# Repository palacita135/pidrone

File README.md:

# pidrone
python scripts for dronekit

Setup first your quad with good PID setting before using dronekit

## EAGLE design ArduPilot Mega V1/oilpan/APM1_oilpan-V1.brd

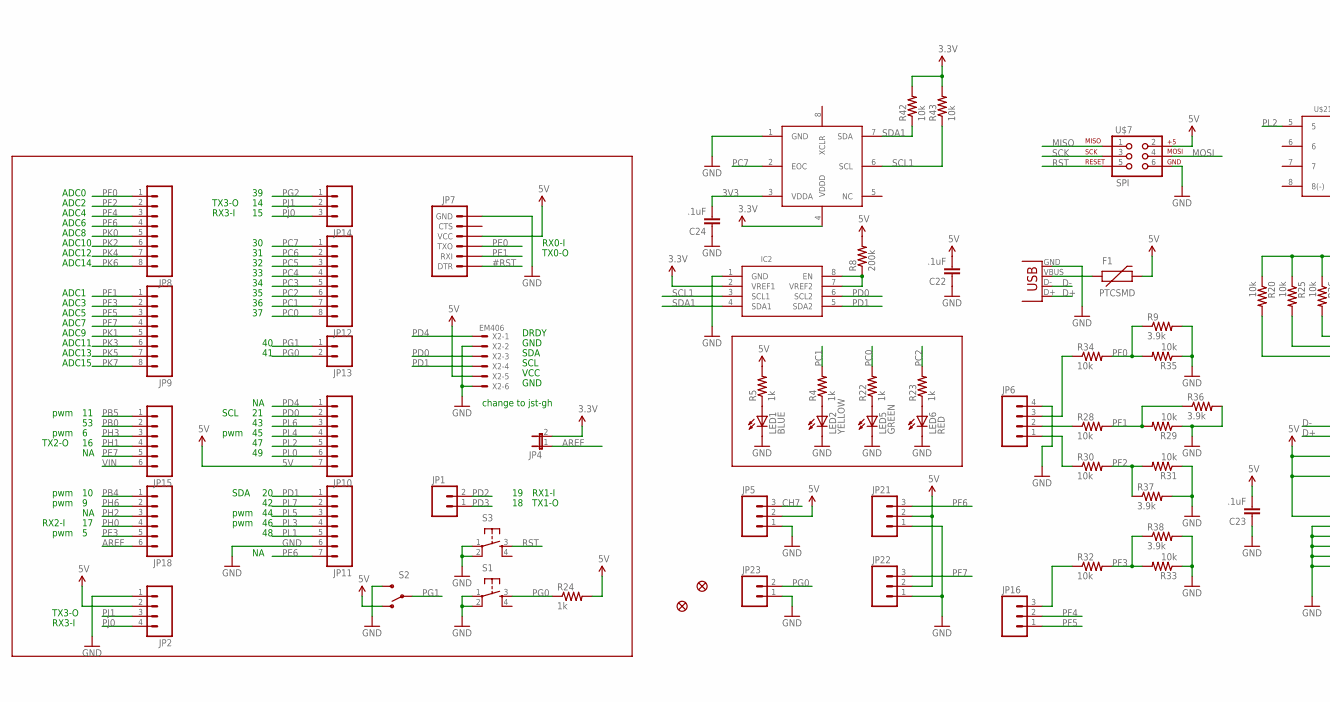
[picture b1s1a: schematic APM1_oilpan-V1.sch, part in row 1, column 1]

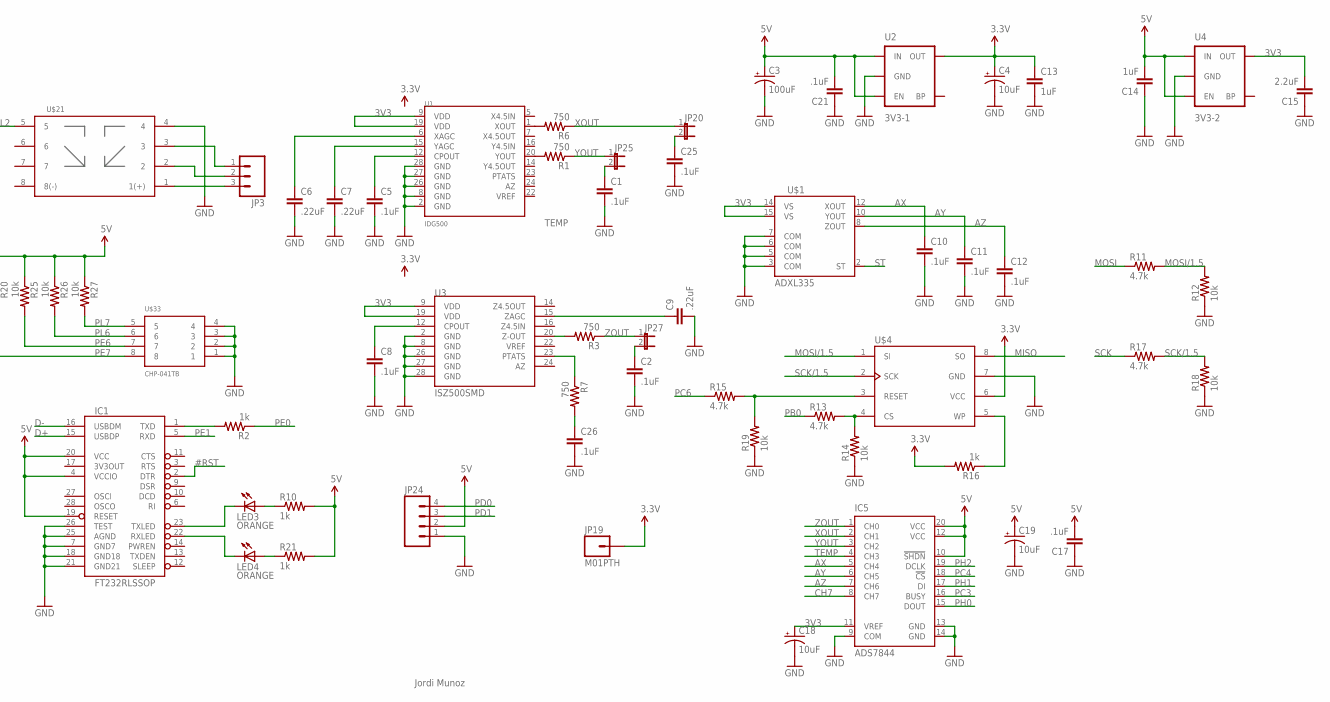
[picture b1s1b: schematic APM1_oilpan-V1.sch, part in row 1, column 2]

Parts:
C1, C2, C5, C8, C10, C11, C12, C17, C21, C22, C23, C24, C25, C26: .1uF; C0402
C3: 100uF; EIA3528
C4, C18, C19: 10uF; EIA3216
C6, C7, C9: .22uF; C0402
C13, C14: 1uF; C0402
C15: 2.2uF; C0402
F1: PTCSMD; PTC-1206
IC1: FT232RLSSOP; SSOP28DB
IC2: PCA9306; SOIC8
IC5: ADS7844; SSOP20BU
JP1, JP13, JP23: M02PTH; 1X02
JP2, JP6, JP24: M04PTH; 1X04
JP3, JP5, JP14, JP16, JP21, JP22: M03PTH; 1X03
JP4, JP20, JP25, JP27: JUMPER-2SMD-NO; SJ_2S-NO
JP7: ARDUINO_SERIAL_PROGRAMPTH; 1X06
JP8, JP9, JP12: M08; 1X08
JP10, JP11: M07; 1X07
JP15, JP18: M06SIP; 1X06
JP17, JP26: FIDUCIAL1X2.5; FIDUCIAL-1X2.5
JP19: M01PTH; 1X01
LED1: BLUE; LED-0603
LED2: YELLOW; LED-0603
LED3, LED4: ORANGE; LED-0603
LED5: GREEN; LED-0603
LED6: RED; LED-0603
R1, R3, R6, R7: 750; C0402
R2, R4, R5, R10, R16, R21, R22, R23, R24: 1k; C0402
R8: 200k; C0402
R9, R36, R37, R38: 3.9k; C0402
R11, R13, R15, R17: 4.7k; C0402
R12, R14, R18, R19, R20, R25, R26, R27, R28, R30, R32, R34, R42, R43: 10k; C0402
R29, R31, R33, R35: 10k; AXIAL-0.3
S1, S3: TAC_SWITCHSMD; TACTILE_SWITCH_SMD
S2: SWITCH-SPSTSMD2; SWITCH-SPDT-SMD
U1: IDG500; QFN-28_6X8
U2: 3V3-1; SOT23-5
U3: ISZ500SMD; QFN-28_6X8
U4: 3V3-2; SOT23-5
U$1: ADXL335; LFCSP-16
U$4: DF; SO08WIDE
U$7: SPI; 2X3-NS
U$8: BMP085
U$21: RELAY_23
U$33: CHP-041TB
X1: USBSMD; USB-MINIB
X2: EM406; GH-06V

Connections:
3.3V: C4.A (+), C13.1, IC2.2 (VREF1), JP4.2, JP19.1, R16.2, R42.2, R43.2, U2.5 (OUT), U$4.6 (VCC), U$8.4 (VDDD)
3V3: C15.2, C18.A (+), C24.2, IC5.11 (VREF), U1.9 (VDD), U1.19 (VDD), U3.9 (VDD), U3.19 (VDD), U4.5 (OUT), U$1.14 (VS), U$1.15 (VS), U$8.3 (VDDA)
5V: C3.A (+), C14.2, C17.2, C19.A (+), C21.2, C22.2, C23.2, F1.2, IC1.4 (VCCIO), IC1.19 (RESET), IC1.20 (VCC), IC5.10 (!SHDN), IC5.12 (VCC), IC5.20 (VCC), JP2.2, JP5.2, JP7.4 (VCC), JP10.7, JP21.2, JP22.2, JP24.2, R5.2, R8.2, R10.2, R20.1, R21.2, R24.2, R25.1, R26.1, R27.1, S2.1 (O), U2.1 (IN), U2.3 (EN), U4.1 (IN), U4.3 (EN), U$7.2, X2.5
8(-): U$21.8 (8(-))
#RST: IC1.2 (DTR), JP7.1 (DTR)
AREF: JP4.1, JP18.6
AX: C10.1, IC5.5 (CH4), U$1.12 (XOUT)
AY: C11.1, IC5.6 (CH5), U$1.10 (YOUT)
AZ: C12.1, IC5.7 (CH6), U$1.8 (ZOUT)
CH7: IC5.8 (CH7), JP5.3
D+: IC1.15 (USBDP), X1.D+
D-: IC1.16 (USBDM), X1.D-
GND: C1.2, C2.2, C3.C (-), C4.C (-), C5.2, C6.2, C7.2, C8.2, C9.2, C10.2, C11.2, C12.2, C13.2, C14.1, C15.1, C17.1, C18.C (-), C19.C (-), C21.1, C22.1, C23.1, C24.1, C25.2, C26.2, IC1.7 (GND7), IC1.18 (GND18), IC1.21 (GND21), IC1.25 (AGND), IC1.26 (TEST), IC2.1 (GND), IC5.9 (COM), IC5.13 (GND), IC5.14 (GND), JP2.1, JP5.1, JP6.4, JP7.6 (GND), JP11.6, JP21.1, JP22.1, JP23.1, JP24.1, LED1.C, LED2.C, LED5.C, LED6.C, R9.2, R12.1, R14.1, R18.1, R19.1, R29.P$1 (1), R31.P$1 (1), R33.P$1 (1), R35.P$1 (1), R36.2, R37.2, R38.2, S1.1, S1.2, S2.3 (S), S3.1, S3.2, U1.2 (GND), U1.8 (GND), U1.26 (GND), U1.27 (GND), U1.28 (GND), U2.2 (GND), U3.2 (GND), U3.8 (GND), U3.26 (GND), U3.27 (GND), U3.28 (GND), U4.2 (GND), U$1.3 (COM), U$1.5 (COM), U$1.6 (COM), U$1.7 (COM), U$4.7 (GND), U$7.6, U$8.1 (GND), U$21.4, U$33.1, U$33.2, U$33.3, U$33.4, X1.GND, X2.2, X2.6
MISO: U$4.8 (SO), U$7.1
MOSI: R11.1, U$7.4
MOSI/1.5: R11.2, R12.2, U$4.1 (SI)
unnamed: LED1.A, R5.1
unnamed: LED2.A, R4.1
unnamed: C8.1, U3.12 (CPOUT)
unnamed: C9.1, U3.15 (ZAGC)
unnamed: LED3.A, R10.1
unnamed: IC1.1 (TXD), R2.2
unnamed: R15.2, R19.2, U$4.3 (RESET)
unnamed: R3.2, U3.20 (Z-OUT)
unnamed: R7.1, U3.23 (PTATS)
unnamed: IC2.7 (VREF2), IC2.8 (EN), R8.1
unnamed: JP3.1, U$21.3
unnamed: R1.2, U1.20 (YOUT)
unnamed: C6.1, U1.6 (XAGC)
unnamed: R13.2, R14.2, U$4.4 (CS)
unnamed: R6.2, U1.1 (XOUT)
unnamed: C5.1, U1.12 (CPOUT)
unnamed: F1.1, X1.VBUS
unnamed: C7.1, U1.15 (YAGC)
unnamed: C2.1, JP27.2
unnamed: JP3.2, U$21.2
unnamed: LED4.A, R21.1
unnamed: C25.1, JP20.2
unnamed: IC1.23 (TXLED), LED3.C
unnamed: IC1.22 (RXLED), LED4.C
unnamed: LED5.A, R22.1
unnamed: LED6.A, R23.1
unnamed: JP3.3, U$21.1 (1(+))
unnamed: C1.1, JP25.2
unnamed: JP6.2, R28.1
unnamed: JP6.1, R30.1
unnamed: JP16.3, R32.1
unnamed: JP6.3, R34.1
PB0: JP15.2, R13.1
PB4: JP18.1
PB5: JP15.1
PC0: JP12.8, R22.2
PC1: JP12.7, R4.2
PC2: JP12.6, R23.2
PC3: IC5.16 (BUSY), JP12.5
PC4: IC5.18 (!CS), JP12.4
PC5: JP12.3
PC6: JP12.2, R15.1
PC7: JP12.1, U$8.2 (EOC)
PD0: IC2.6 (SCL2), JP10.2, JP24.4, X2.3
PD1: IC2.5 (SDA2), JP11.1, JP24.3, X2.4
PD2: JP1.2
PD3: JP1.1
PD4: JP10.1, X2.1
PE0: JP7.3 (TXO), R2.1
PE1: IC1.5 (RXD), JP7.2 (RXI)
PE3: JP18.5
PE6: JP11.7, R25.2, U$33.7
PE7: JP15.5, R20.2, U$33.8
PF0: JP8.1, R9.1, R34.2, R35.P$2 (2)
PF1: JP9.1, R28.2, R29.P$2 (2), R36.1
PF2: JP8.2, R30.2, R31.P$2 (2), R37.1
PF3: JP9.2, R32.2, R33.P$2 (2), R38.1
PF4: JP8.3, JP16.2
PF5: JP9.3, JP16.1
PF6: JP8.4, JP21.3
PF7: JP9.4, JP22.3
PG0: JP13.2, JP23.2, R24.1, S1.3
PG1: JP13.1, S2.2
PG2: JP14.1
PH0: IC5.15 (DOUT), JP18.4
PH1: IC5.17 (DI), JP15.4
PH2: IC5.19 (DCLK), JP18.3
PH3: JP15.3
PH6: JP18.2
PJ0: JP2.4, JP14.3
PJ1: JP2.3, JP14.2
PK0: JP8.5
PK1: JP9.5
PK2: JP8.6
PK3: JP9.6
PK4: JP8.7
PK5: JP9.7
PK6: JP8.8
PK7: JP9.8
PL0: JP10.6
PL1: JP11.5
PL2: JP10.5, U$21.5
PL3: JP11.4
PL4: JP10.4
PL5: JP11.3
PL6: JP10.3, R26.2, U$33.6
PL7: JP11.2, R27.2, U$33.5
RST: S3.3, U$7.5
SCK: R17.1, U$7.3
SCK/1.5: R17.2, R18.2, U$4.2 (SCK)
SCL1: IC2.3 (SCL1), R43.1, U$8.6 (SCL)
SDA1: IC2.4 (SDA1), R42.1, U$8.7 (SDA)
ST: U$1.2 (ST)
TEMP: C26.1, IC5.4 (CH3), R7.2
VIN: JP15.6
WP: R16.1, U$4.5 (WP)
XOUT: IC5.2 (CH1), JP20.1, R6.1
YOUT: IC5.3 (CH2), JP25.1, R1.1
ZOUT: IC5.1 (CH0), JP27.1, R3.1

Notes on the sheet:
ADC0
ADC1
ADC2
ADC3
ADC4
ADC5
ADC6
ADC7
ADC8
ADC9
ADC10
ADC11
ADC12
ADC13
ADC14
ADC15
GND
VCC
DRDY
RX1-I
TX1-O
TX0-O
RX0-I
RX2-I
TX2-O
TX3-O
RX3-I
SDA
SCL
pwm
Jordi Munoz
change to jst-gh

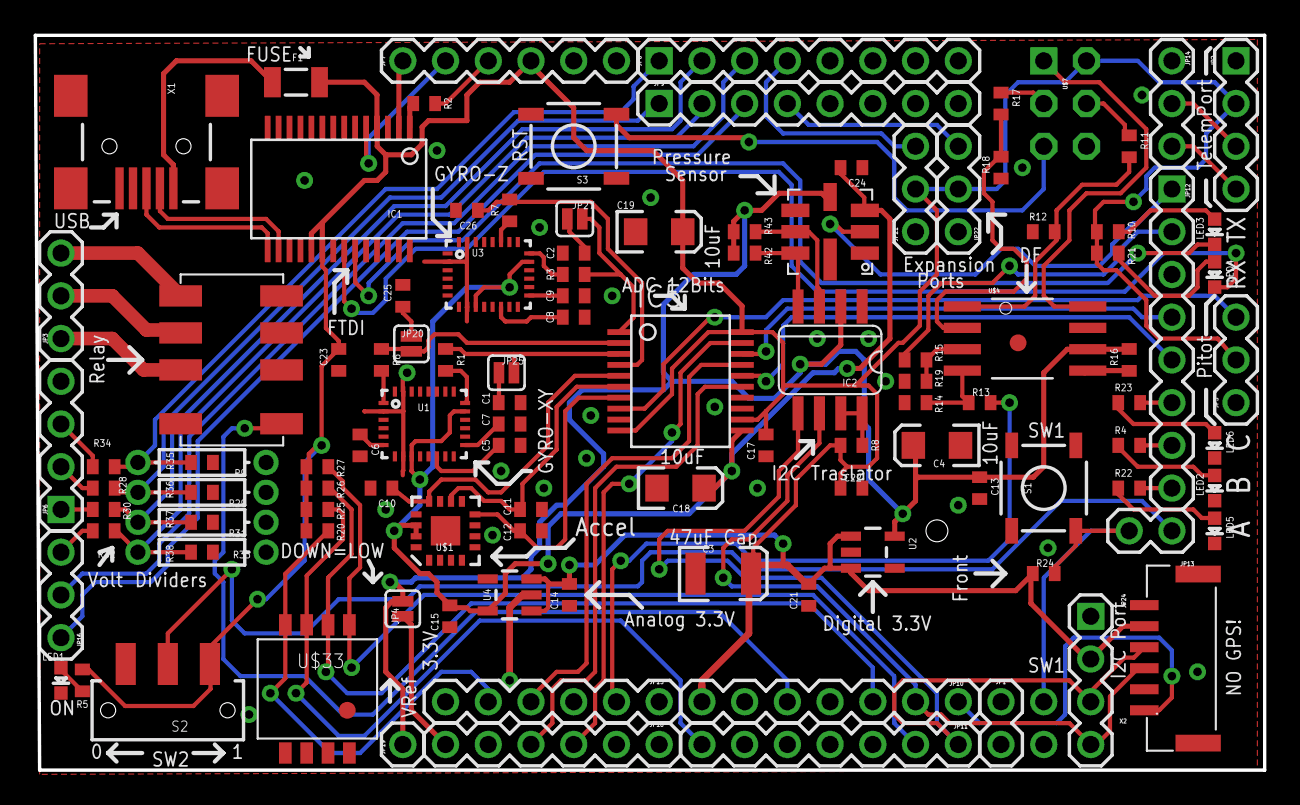
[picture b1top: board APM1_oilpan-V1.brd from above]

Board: 2 copper layers, 73.1 x 43.7 mm, 116 parts (1 on the bottom side), 90 nets.

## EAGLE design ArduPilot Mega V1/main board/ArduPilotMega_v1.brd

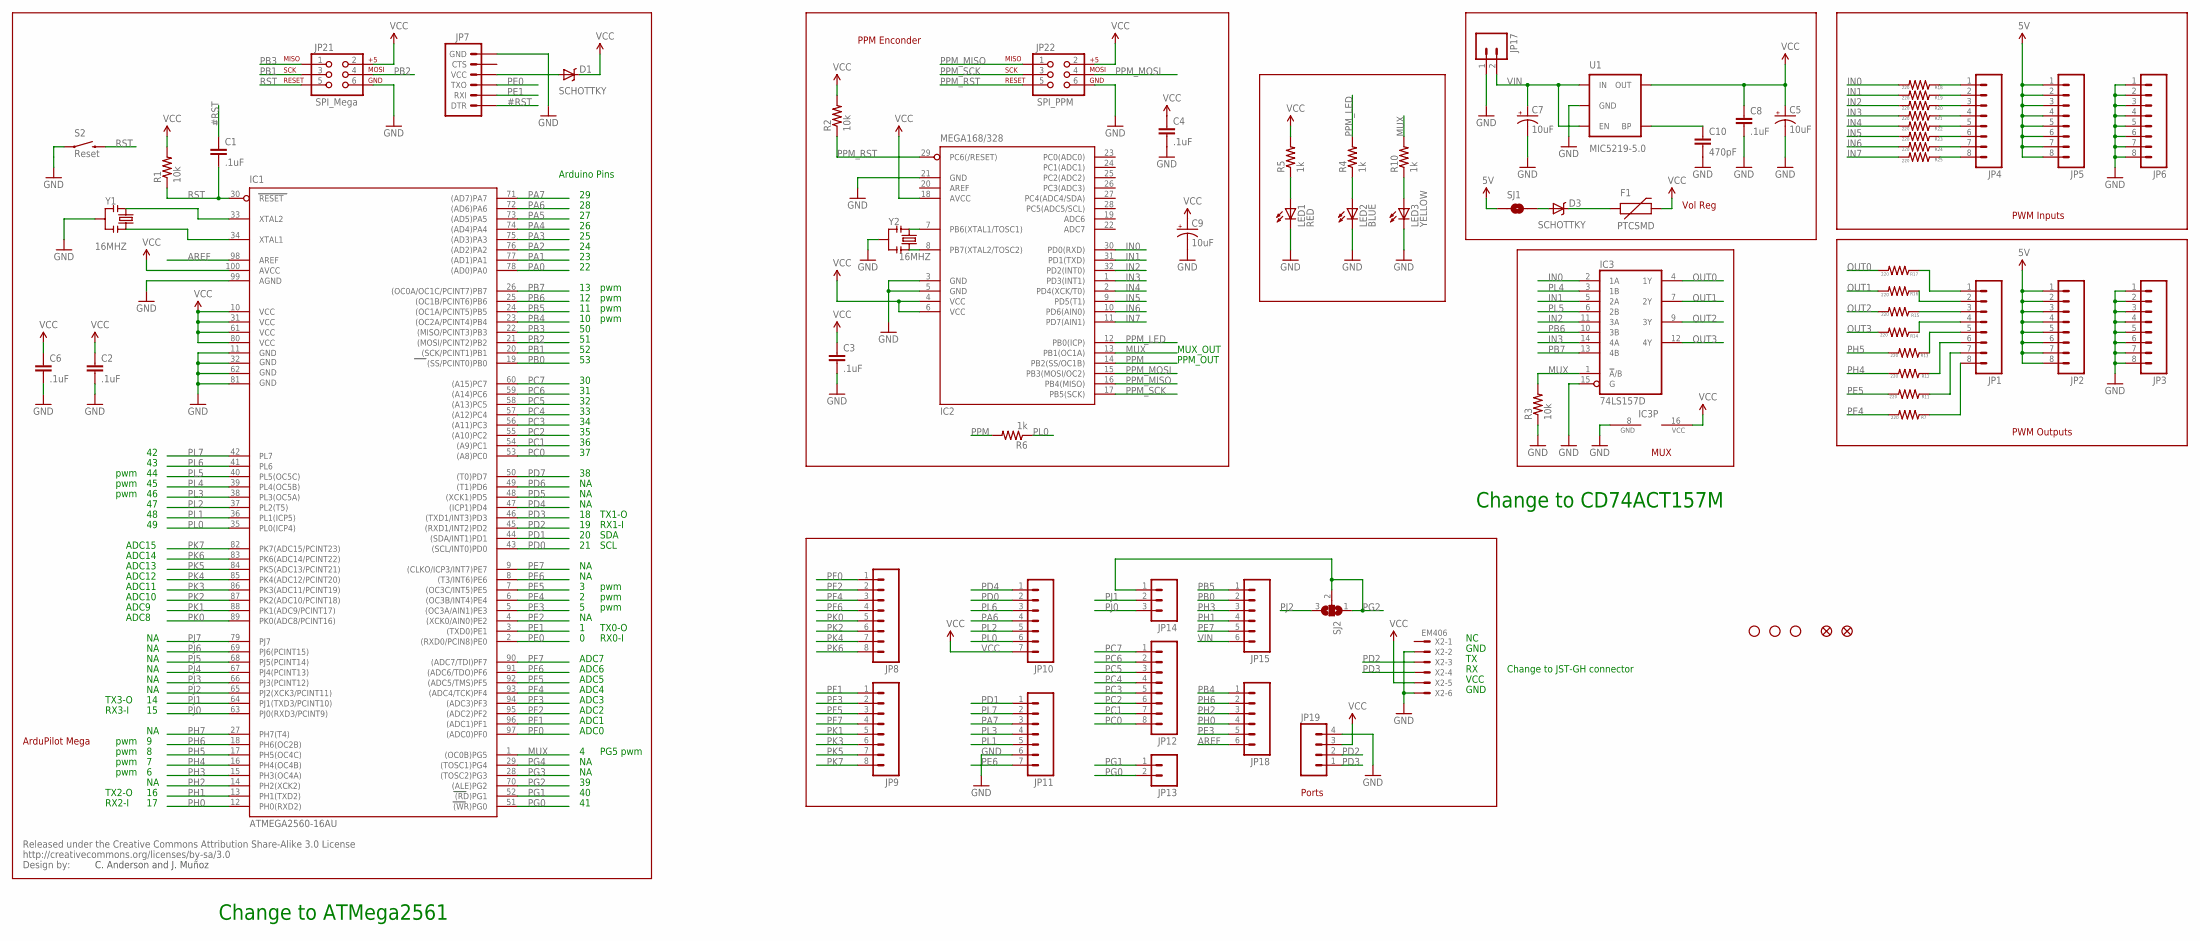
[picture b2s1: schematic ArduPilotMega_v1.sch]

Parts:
C1, C2, C3, C4, C6, C8: .1uF; C0402
C5, C7, C9: 10uF; EIA3216
C10: 470pF; C0402
D1, D3: SCHOTTKY; SMA-DIODE
F1: PTCSMD; PTC-1206
IC1: ATMEGA2560-16AU; TQFP100
IC2: MEGA168/328; TQFP32-08
IC3: 74LS157D; SO16
JP1, JP2, JP3, JP4, JP5, JP6, JP8, JP9, JP12: M08; 1X08
JP7: ARDUINO_SERIAL_PROGRAMPTH; 1X06
JP10, JP11: M07; 1X07
JP13: M02PTH; 1X02
JP14: M03PTH; 1X03
JP15, JP18: M06SIP; 1X06
JP16, JP20: FIDUCIAL1X2; FIDUCIAL-1X2
JP17: M02NG; 1X02
JP19: M04PTH; 1X04
JP21: SPI_Mega; 2X3-NS
JP22: SPI_PPM; 2X3-NS
LED1: RED; LED-0603
LED2: BLUE; LED-0603
LED3: YELLOW; LED-0603
R1, R2, R3: 10k; C0402
R4, R5, R6, R10: 1k; C0402
R7, R11, R12, R13, R14, R15, R16, R17, R18, R19, R20, R21, R22, R23, R24, R25: 220; C0402
S2: Reset; TACTILE_SWITCH_SMD
SJ1: SJ2; SJ_2S
SJ2: SOLDERJUMPER_2WAYS; SJ_3
U1: MIC5219-5.0; SOT23-5
U$8: CREATIVE_COMMONS
U$10, U$12, U$13: STAND-OFF
X2: EM406; GH-06V
Y1, Y2: 16MHZ; RESONATOR-SMD

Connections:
5V: JP2.1, JP2.2, JP2.3, JP2.4, JP2.5, JP2.6, JP2.7, JP2.8, JP5.1, JP5.2, JP5.3, JP5.4, JP5.5, JP5.6, JP5.7, JP5.8, SJ1.1
#RST: C1.1, JP7.1 (DTR)
AREF: IC1.98 (AREF), JP18.6
GND: C2.2, C3.2, C4.2, C5.C (-), C6.2, C7.C (-), C8.2, C9.C (-), C10.2, IC1.11 (GND), IC1.32 (GND1), IC1.62 (GND2), IC1.81 (GND3), IC1.99 (AGND), IC2.3 (GND), IC2.5 (GND), IC2.21 (GND), IC3.8 (GND), IC3.15 (G), JP3.1, JP3.2, JP3.3, JP3.4, JP3.5, JP3.6, JP3.7, JP3.8, JP6.1, JP6.2, JP6.3, JP6.4, JP6.5, JP6.6, JP6.7, JP6.8, JP7.6 (GND), JP11.6, JP17.1, JP19.4, JP21.6, JP22.6, LED1.C, LED2.C, LED3.C, R3.1, S2.1, U1.2 (GND), X2.2, X2.6, Y1.2, Y2.2
IN0: IC2.30 (PD0(RXD)), IC3.2 (1A), R18.2
IN1: IC2.31 (PD1(TXD)), IC3.5 (2A), R19.2
IN2: IC2.32 (PD2(INT0)), IC3.11 (3A), R20.2
IN3: IC2.1 (PD3(INT1)), IC3.14 (4A), R21.2
IN4: IC2.2 (PD4(XCK/T0)), R22.2
IN5: IC2.9 (PD5(T1)), R23.2
IN6: IC2.10 (PD6(AIN0)), R24.2
IN7: IC2.11 (PD7(AIN1)), R25.2
MUX: IC1.1 ((OC0B)PG5), IC2.13 (PB1(OC1A)), IC3.1 (!A!/B), R3.2, R10.2
unnamed: LED1.A, R5.1
unnamed: LED2.A, R4.1
unnamed: C10.1, U1.4 (BP)
unnamed: LED3.A, R10.1
unnamed: IC2.7 (PB6(XTAL1/TOSC1)), Y2.1
unnamed: IC2.8 (PB7(XTAL2/TOSC2)), Y2.3
unnamed: JP1.5, R13.1
unnamed: JP1.6, R12.1
unnamed: JP1.7, R11.1
unnamed: JP1.8, R7.1
unnamed: JP1.4, R14.1
unnamed: JP1.3, R15.1
unnamed: JP1.2, R16.1
unnamed: JP1.1, R17.1
unnamed: D3.A, SJ1.2
unnamed: JP4.1, R18.1
unnamed: JP4.2, R19.1
unnamed: JP4.3, R20.1
unnamed: JP4.4, R21.1
unnamed: JP4.5, R22.1
unnamed: JP4.6, R23.1
unnamed: JP4.7, R24.1
unnamed: JP4.8, R25.1
unnamed: D3.C, F1.1
unnamed: D1.A, JP7.4 (VCC)
unnamed: IC1.34 (XTAL1), Y1.3
unnamed: IC1.33 (XTAL2), Y1.1
OUT0: IC3.4 (1Y), R17.2
OUT1: IC3.7 (2Y), R16.2
OUT2: IC3.9 (3Y), R15.2
OUT3: IC3.12 (4Y), R14.2
PA0: IC1.78 ((AD0)PA0)
PA1: IC1.77 ((AD1)PA1)
PA2: IC1.76 ((AD2)PA2)
PA3: IC1.75 ((AD3)PA3)
PA4: IC1.74 ((AD4)PA4)
PA5: IC1.73 ((AD5)PA5)
PA6: IC1.72 ((AD6)PA6), JP10.4
PA7: IC1.71 ((AD7)PA7), JP11.3
PB0: IC1.19 ((SS/PCINT0)PB0), JP15.2
PB1: IC1.20 ((SCK/PCINT1)PB1), JP21.3
PB2: IC1.21 ((MOSI/PCINT2)PB2), JP21.4
PB3: IC1.22 ((MISO/PCINT3)PB3), JP21.1
PB4: IC1.23 ((OC2A/PCINT4)PB4), JP18.1
PB5: IC1.24 ((OC1A/PCINT5)PB5), JP15.1
PB6: IC1.25 ((OC1B/PCINT6)PB6), IC3.10 (3B)
PB7: IC1.26 ((OC0A/OC1C/PCINT7)PB7), IC3.13 (4B)
PC0: IC1.53 ((A8)PC0), JP12.8
PC1: IC1.54 ((A9)PC1), JP12.7
PC2: IC1.55 ((A10)PC2), JP12.6
PC3: IC1.56 ((A11)PC3), JP12.5
PC4: IC1.57 ((A12)PC4), JP12.4
PC5: IC1.58 ((A13)PC5), JP12.3
PC6: IC1.59 ((A14)PC6), JP12.2
PC7: IC1.60 ((A15)PC7), JP12.1
PD0: IC1.43 ((SCL/INT0)PD0), JP10.2
PD1: IC1.44 ((SDA/INT1)PD1), JP11.1
PD2: IC1.45 ((RXD1/INT2)PD2), JP19.2, X2.3
PD3: IC1.46 ((TXD1/INT3)PD3), JP19.1, X2.4
PD4: IC1.47 ((ICP1)PD4), JP10.1
PD5: IC1.48 ((XCK1)PD5)
PD6: IC1.49 ((T1)PD6)
PD7: IC1.50 ((T0)PD7)
PE0: IC1.2 ((RXD0/PCIN8)PE0), JP7.3 (TXO)
PE1: IC1.3 ((TXD0)PE1), JP7.2 (RXI)
PE2: IC1.4 ((XCK0/AIN0)PE2)
PE3: IC1.5 ((OC3A/AIN1)PE3), JP18.5
PE4: IC1.6 ((OC3B/INT4)PE4), R7.2
PE5: IC1.7 ((OC3C/INT5)PE5), R11.2
PE6: IC1.8 ((T3/INT6)PE6), JP11.7
PE7: IC1.9 ((CLKO/ICP3/INT7)PE7), JP15.5
PF0: IC1.97 ((ADC0)PF0), JP8.1
PF1: IC1.96 ((ADC1)PF1), JP9.1
PF2: IC1.95 ((ADC2)PF2), JP8.2
PF3: IC1.94 ((ADC3)PF3), JP9.2
PF4: IC1.93 ((ADC4/TCK)PF4), JP8.3
PF5: IC1.92 ((ADC5/TMS)PF5), JP9.3
PF6: IC1.91 ((ADC6/TDO)PF6), JP8.4
PF7: IC1.90 ((ADC7/TDI)PF7), JP9.4
PG0: IC1.51 ((WR)PG0), JP13.2
PG1: IC1.52 ((RD)PG1), JP13.1
PG2: IC1.70 ((ALE)PG2), JP14.1, SJ2.1, SJ2.2
PG3: IC1.28 ((TOSC2)PG3)
PG4: IC1.29 ((TOSC1)PG4)
PH0: IC1.12 (PH0(RXD2)), JP18.4
PH1: IC1.13 (PH1(TXD2)), JP15.4
PH2: IC1.14 (PH2(XCK2)), JP18.3
PH3: IC1.15 (PH3(OC4A)), JP15.3
PH4: IC1.16 (PH4(OC4B)), R12.2
PH5: IC1.17 (PH5(OC4C)), R13.2
PH6: IC1.18 (PH6(OC2B)), JP18.2
PH7: IC1.27 (PH7(T4))
PJ0: IC1.63 (PJ0(RXD3/PCINT9)), JP14.3
PJ1: IC1.64 (PJ1(TXD3/PCINT10)), JP14.2
PJ2: IC1.65 (PJ2(XCK3/PCINT11)), SJ2.3
PJ3: IC1.66 (PJ3(PCINT12))
PJ4: IC1.67 (PJ4(PCINT13))
PJ5: IC1.68 (PJ5(PCINT14))
PJ6: IC1.69 (PJ6(PCINT15))
PJ7: IC1.79 (PJ7)
PK0: IC1.89 (PK0(ADC8/PCINT16)), JP8.5
PK1: IC1.88 (PK1(ADC9/PCINT17)), JP9.5
PK2: IC1.87 (PK2(ADC10/PCINT18)), JP8.6
PK3: IC1.86 (PK3(ADC11/PCINT19)), JP9.6
PK4: IC1.85 (PK4(ADC12/PCINT20)), JP8.7
PK5: IC1.84 (PK5(ADC13/PCINT21)), JP9.7
PK6: IC1.83 (PK6(ADC14/PCINT22)), JP8.8
PK7: IC1.82 (PK7(ADC15/PCINT23)), JP9.8
PL0: IC1.35 (PL0(ICP4)), JP10.6, R6.1
PL1: IC1.36 (PL1(ICP5)), JP11.5
PL2: IC1.37 (PL2(T5)), JP10.5
PL3: IC1.38 (PL3(OC5A)), JP11.4
PL4: IC1.39 (PL4(OC5B)), IC3.3 (1B)
PL5: IC1.40 (PL5(OC5C)), IC3.6 (2B)
PL6: IC1.41 (PL6), JP10.3
PL7: IC1.42 (PL7), JP11.2
PPM: IC2.14 (PB2(SS/OC1B)), R6.2
PPM_LED: IC2.12 (PB0(ICP)), R4.2
PPM_MISO: IC2.16 (PB4(MISO)), JP22.1
PPM_MOSI: IC2.15 (PB3(MOSI/OC2)), JP22.4
PPM_RST: IC2.29 (PC6(/RESET)), JP22.5, R2.1
PPM_SCK: IC2.17 (PB5(SCK)), JP22.3
RST: C1.2, IC1.30 (RESET), JP21.5, R1.1, S2.3 (2)
VCC: C2.1, C3.1, C4.1, C5.A (+), C6.1, C8.1, C9.A (+), D1.C, F1.2, IC1.10 (VCC), IC1.31 (VCC1), IC1.61 (VCC2), IC1.80 (VCC3), IC1.100 (AVCC), IC2.4 (VCC), IC2.6 (VCC), IC2.18 (AVCC), IC3.16 (VCC), JP10.7, JP19.3, JP21.2, JP22.2, R1.2, R2.2, R5.2, U1.5 (OUT), X2.5
VIN: C7.A (+), JP15.6, JP17.2, U1.1 (IN), U1.3 (EN)

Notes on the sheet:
ADC0
ADC1
ADC2
ADC3
ADC4
ADC5
ADC6
ADC7
ADC8
ADC9
ADC10
ADC11
ADC12
ADC13
ADC14
ADC15
PPM_OUT
MUX_OUT
GND
VCC
RX1-I
TX1-O
TX0-O
RX0-I
RX2-I
TX2-O
TX3-O
RX3-I
SDA
SCL
pwm
PG5 pwm
PWM Outputs
PWM Inputs
MUX
Vol Reg
PPM Enconder
Ports
ArduPilot Mega
Arduino Pins

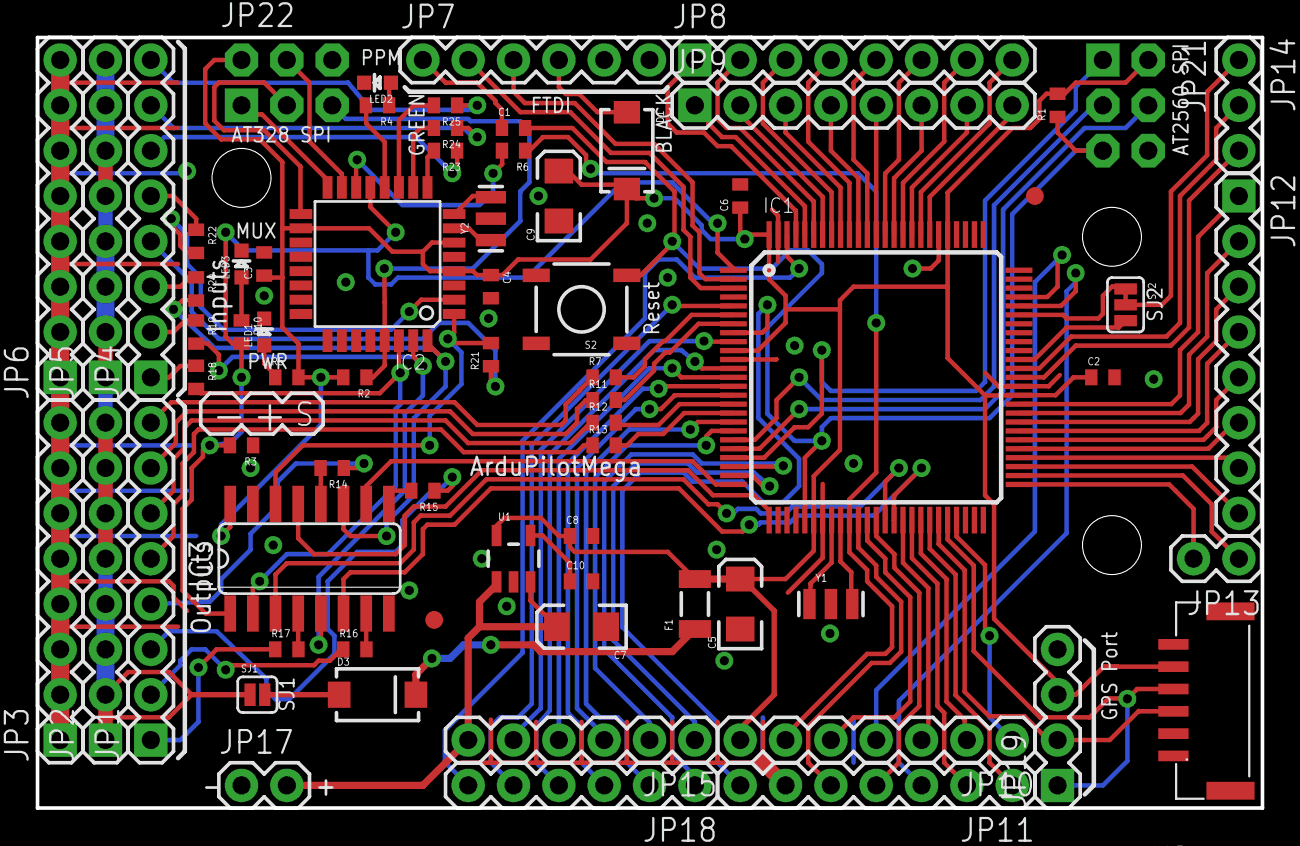
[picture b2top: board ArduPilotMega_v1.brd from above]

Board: 2 copper layers, 68.6 x 43.2 mm, 75 parts (0 on the bottom side), 120 nets.

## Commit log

2021-06-28 version takeoff - hover - land quad
2021-06-28 step of install dronekit to your pi
2021-06-29 Create RPi Network
    Script communicate over network
    The current settings in MAVProxy are:
    Setting Description Value Range
    link Primary Link number -1 to 4
    streamrate Data stream rate on link 1 -1 to 100
    streamrate2 Data stream rate on link 2 -1 to 100
2021-06-29 Create MAVProxy cheatsheet
2021-06-30 Create SITL
2021-06-30 Update SITL
2021-06-30 Create RPi NAS
2021-07-01 Create mission_basic
2021-07-02 Create Gazebo_Simulator
2021-07-05 Create sim_vehicle.py -w
2021-07-05 Update sim_vehicle.py -w
2021-07-06 Create picamera
2021-07-06 Create coordinate_home
2021-07-06 Create clover_vm
2021-07-06 Create opencv
2021-07-06 Update opencv
2021-07-06 Create opencv-raspi4
2021-07-06 Create instaling-ardupilot
2021-07-06 Create installing-gazebo-ardupilot
2021-07-06 Create simulasi-istu
2021-07-06 Create mission-script
2021-07-07 Update mission-script
2021-07-07 Create aruco_test
2021-07-07 Update aruco_test
2021-07-08 Create dronekit
2021-07-08 Create opencv_install
2021-07-08 Update opencv_install
2021-07-09 Update simulasi-istu
2021-07-12 Create aruco_aug
2021-07-12 Update aruco_aug
2021-07-21 Create pycharm_aruco_pose
2021-07-21 Update pycharm_aruco_pose
2021-08-10 installing ws2812b, running with sudo python3
2021-08-30 delivery drone with led
2021-09-21 testing led
2021-10-10 Create raspberrypi_LED
2021-10-10 Update raspberrypi_LED
2021-10-13 Create COEX
2021-10-13 Create coexflight.py
    for coex OS
2021-11-12 Create install mono
2021-11-12 Update install mono
2022-06-17 Create 4G - LTE drone Raspberry pi4
2022-06-17 Update 4G - LTE drone Raspberry pi4
2022-06-25 Update RPi NAS
2022-06-26 Update instaling-ardupilot
2022-07-11 use for SITL

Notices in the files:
parts and their libraries:
SparkFun: Released under the Creative Commons Attribution Share-Alike 3.0 License
SparkFun: http://creativecommons.org/licenses/by-sa/3.0
